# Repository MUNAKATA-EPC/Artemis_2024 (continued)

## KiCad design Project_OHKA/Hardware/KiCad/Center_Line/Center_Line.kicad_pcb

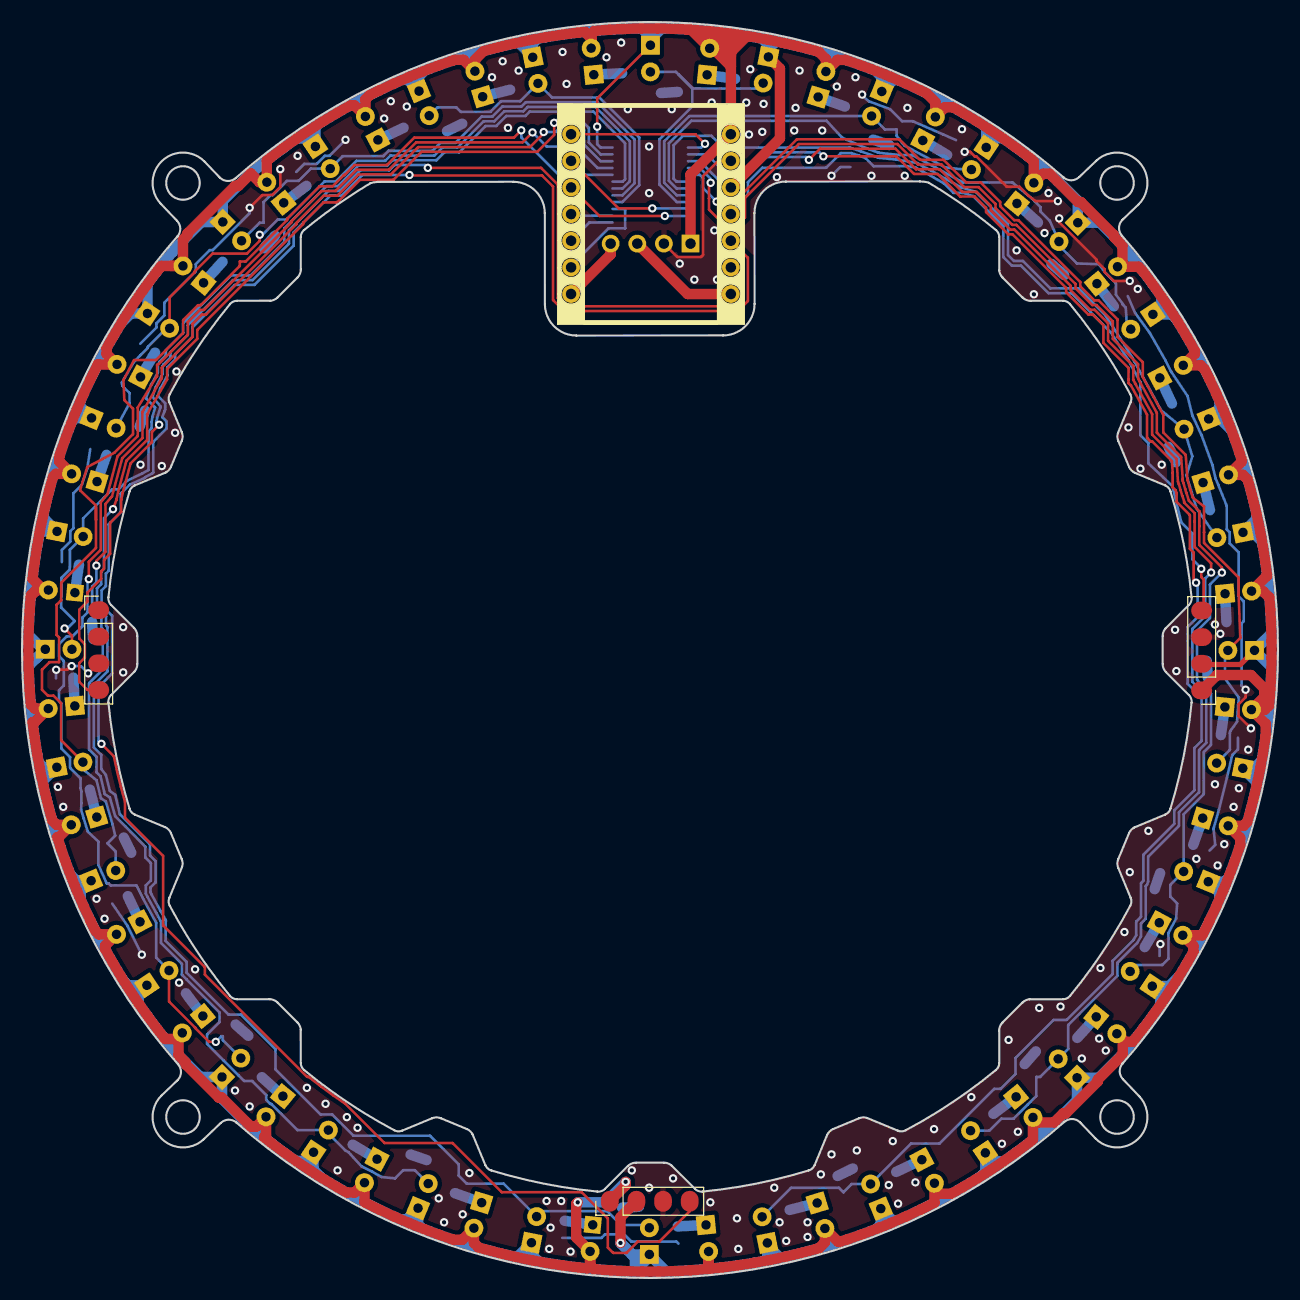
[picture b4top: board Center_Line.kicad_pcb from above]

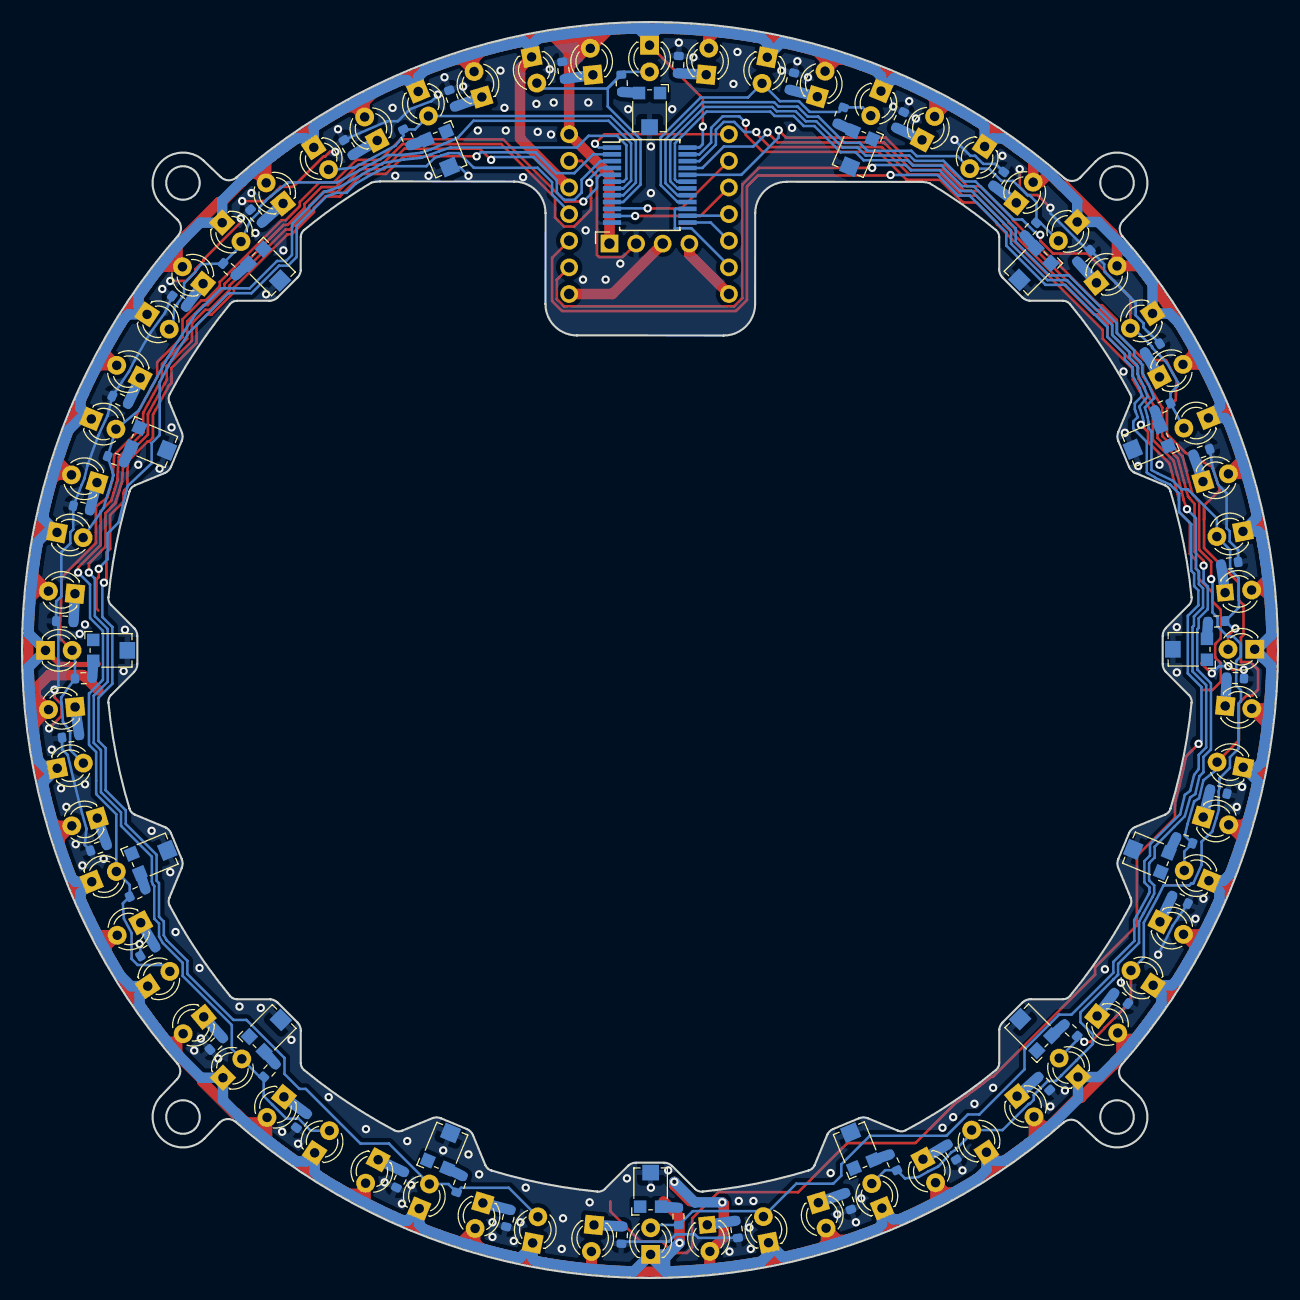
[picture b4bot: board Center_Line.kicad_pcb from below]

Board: 2 copper layers, 119.8 x 119.8 mm, 134 parts (130 on the bottom side), 78 nets.

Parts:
D1, D2, D3, D4, D5, D6, D7, D8, D9, D10, D11, D12, D13, D14, D15, D16, D17, D18, D19, D20, D21, D22, D23, D24, D25, D26, D27, D28, D29, D30, D31, D32: LED; LED_D3.0mm_Clear
J1: Conn_01x04_Socket; PinSocket_1x04_P2.54mm_Horizontal
J2, J3, J4: Conn_01x04_Socket; PinHeader_1x04_P2.54mm_Vertical
Q1, Q2, Q3, Q4, Q5, Q6, Q7, Q8, Q9, Q10, Q11, Q12, Q13, Q14, Q15, Q16, Q17, Q18, Q19, Q20, Q21, Q22, Q23, Q24, Q25, Q26, Q27, Q28, Q29, Q30, Q31, Q32: Q_Photo_NPN; LED_D3.0mm_Clear
R1, R2, R3, R4, R5, R6, R7, R8, R9, R10, R11, R12, R13, R14, R15, R16, R17, R18, R19, R20, R21, R22, R23, R24, R25, R26, R27, R28, R29, R30, R31, R32, R33, R34, R35, R36, R37, R38, R39, R40, R41, R42, R43, R44, R45, R46, R47, R48: R; R_0603_1608Metric
RV1, RV2, RV3, RV4, RV5, RV6, RV7, RV8, RV9, RV10, RV11, RV12, RV13, RV14, RV15, RV16: R_Potentiometer_Trim_US; Potentiometer_Bourns_TC33X_Vertical
U1: CD74HC4067SM; SSOP-24_5.3x8.2mm_P0.65mm
U2: Seeeduino_Xiao; seeeduinoXIAO

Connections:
+3.3V: J2.2, J3.2, J4.2, Q1.1 (C), Q2.1 (C), Q3.1 (C), Q4.1 (C), Q5.1 (C), Q6.1 (C), Q7.1 (C), Q8.1 (C), Q9.1 (C), Q10.1 (C), Q11.1 (C), Q12.1 (C), Q13.1 (C), Q14.1 (C), Q15.1 (C), Q16.1 (C), Q17.1 (C), Q18.1 (C), Q19.1 (C), Q20.1 (C), Q21.1 (C), Q22.1 (C), Q23.1 (C), Q24.1 (C), Q25.1 (C), Q26.1 (C), Q27.1 (C), Q28.1 (C), Q29.1 (C), Q30.1 (C), Q31.1 (C), Q32.1 (C), U1.24 (VCC), U2.12 (3V3)
+5V: D1.2 (A), D2.2 (A), D3.2 (A), D4.2 (A), D5.2 (A), D6.2 (A), D7.2 (A), D8.2 (A), D9.2 (A), D10.2 (A), D11.2 (A), D12.2 (A), D13.2 (A), D14.2 (A), D15.2 (A), D16.2 (A), D17.2 (A), D18.2 (A), D19.2 (A), D20.2 (A), D21.2 (A), D22.2 (A), D23.2 (A), D24.2 (A), D25.2 (A), D26.2 (A), D27.2 (A), D28.2 (A), D29.2 (A), D30.2 (A), D31.2 (A), D32.2 (A), J1.1, J2.1, J3.1, J4.1, U2.14 (5V)
/1: Q1.2 (E), Q2.2 (E), R33.2, U1.9 (I0)
/2: Q3.2 (E), Q4.2 (E), R34.2, U1.8 (I1)
/3: Q5.2 (E), Q6.2 (E), R35.2, U1.7 (I2)
/4: Q7.2 (E), Q8.2 (E), R36.2, U1.6 (I3)
/5: Q9.2 (E), Q10.2 (E), R37.2, U1.5 (I4)
/6: Q11.2 (E), Q12.2 (E), R38.2, U1.4 (I5)
/7: Q13.2 (E), Q14.2 (E), R39.2, U1.3 (I6)
/8: Q15.2 (E), Q16.2 (E), R40.2, U1.2 (I7)
/9: Q17.2 (E), Q18.2 (E), R41.2, U1.23 (I8)
/10: Q19.2 (E), Q20.2 (E), R42.2, U1.22 (I9)
/11: Q21.2 (E), Q22.2 (E), R43.2, U1.21 (I10)
/12: Q23.2 (E), Q24.2 (E), R44.2, U1.20 (I11)
/13: Q25.2 (E), Q26.2 (E), R45.2, U1.19 (I12)
/14: Q27.2 (E), Q28.2 (E), R46.2, U1.18 (I13)
/15: Q29.2 (E), Q30.2 (E), R47.2, U1.17 (I14)
/16: Q31.2 (E), Q32.2 (E), R48.2, U1.16 (I15)
/BACK: J4.4, U2.10 (MISO)
/E: U1.15 (~E), U2.6 (SCL)
/LEFT: J3.4, U2.11 (MOSI)
/LINE_RX: J1.4, U2.7 (TX)
/LINE_TX: J1.3, U2.8 (RX)
/RIGHT: J2.4, U2.9 (SCK)
/S0: U1.10 (S0), U2.2
/S1: U1.11 (S1), U2.3
/S2: U1.14 (S2), U2.4
/S3: U1.13 (S3), U2.5 (SDA)
/com: U1.1 (COM), U2.1 (DAC)
GND: J1.2, J2.3, J3.3, J4.3, R1.1, R2.1, R3.1, R4.1, R5.1, R6.1, R7.1, R8.1, R9.1, R10.1, R11.1, R12.1, R13.1, R14.1, R15.1, R16.1, R17.1, R18.1, R19.1, R20.1, R21.1, R22.1, R23.1, R24.1, R25.1, R26.1, R27.1, R28.1, R29.1, R30.1, R31.1, R32.1, RV1.2, RV2.2, RV3.2, RV4.2, RV5.2, RV6.2, RV7.2, RV8.2, RV9.2, RV10.2, RV11.2, RV12.2, RV13.2, RV14.2, RV15.2, RV16.2, U1.12 (GND), U2.13 (GND)
unnamed: D1.1 (K), R1.2
unnamed: D2.1 (K), R2.2
unnamed: D3.1 (K), R3.2
unnamed: D4.1 (K), R4.2
unnamed: D5.1 (K), R5.2
unnamed: D6.1 (K), R6.2
unnamed: D7.1 (K), R7.2
unnamed: D8.1 (K), R8.2
unnamed: D9.1 (K), R9.2
unnamed: D10.1 (K), R10.2
unnamed: D11.1 (K), R11.2
unnamed: D12.1 (K), R12.2
unnamed: D13.1 (K), R13.2
unnamed: D14.1 (K), R14.2
unnamed: D15.1 (K), R15.2
unnamed: D16.1 (K), R16.2
unnamed: D17.1 (K), R17.2
unnamed: D18.1 (K), R18.2
unnamed: D19.1 (K), R19.2
unnamed: D20.1 (K), R20.2
unnamed: D21.1 (K), R21.2
unnamed: D22.1 (K), R22.2
unnamed: D23.1 (K), R23.2
unnamed: D24.1 (K), R24.2
unnamed: D25.1 (K), R25.2
unnamed: D26.1 (K), R26.2
unnamed: D27.1 (K), R27.2
unnamed: D28.1 (K), R28.2
unnamed: D29.1 (K), R29.2
unnamed: D30.1 (K), R30.2
unnamed: D31.1 (K), R31.2
unnamed: D32.1 (K), R32.2
unnamed: R33.1, RV1.3
unnamed: R34.1, RV2.3
unnamed: R35.1, RV3.3
unnamed: R36.1, RV4.3
unnamed: R37.1, RV5.3
unnamed: R38.1, RV6.3
unnamed: R39.1, RV7.3
unnamed: R40.1, RV8.3
unnamed: R41.1, RV9.3
unnamed: R42.1, RV10.3
unnamed: R43.1, RV11.3
unnamed: R44.1, RV12.3
unnamed: R45.1, RV13.3
unnamed: R46.1, RV14.3
unnamed: R47.1, RV15.3
unnamed: R48.1, RV16.3

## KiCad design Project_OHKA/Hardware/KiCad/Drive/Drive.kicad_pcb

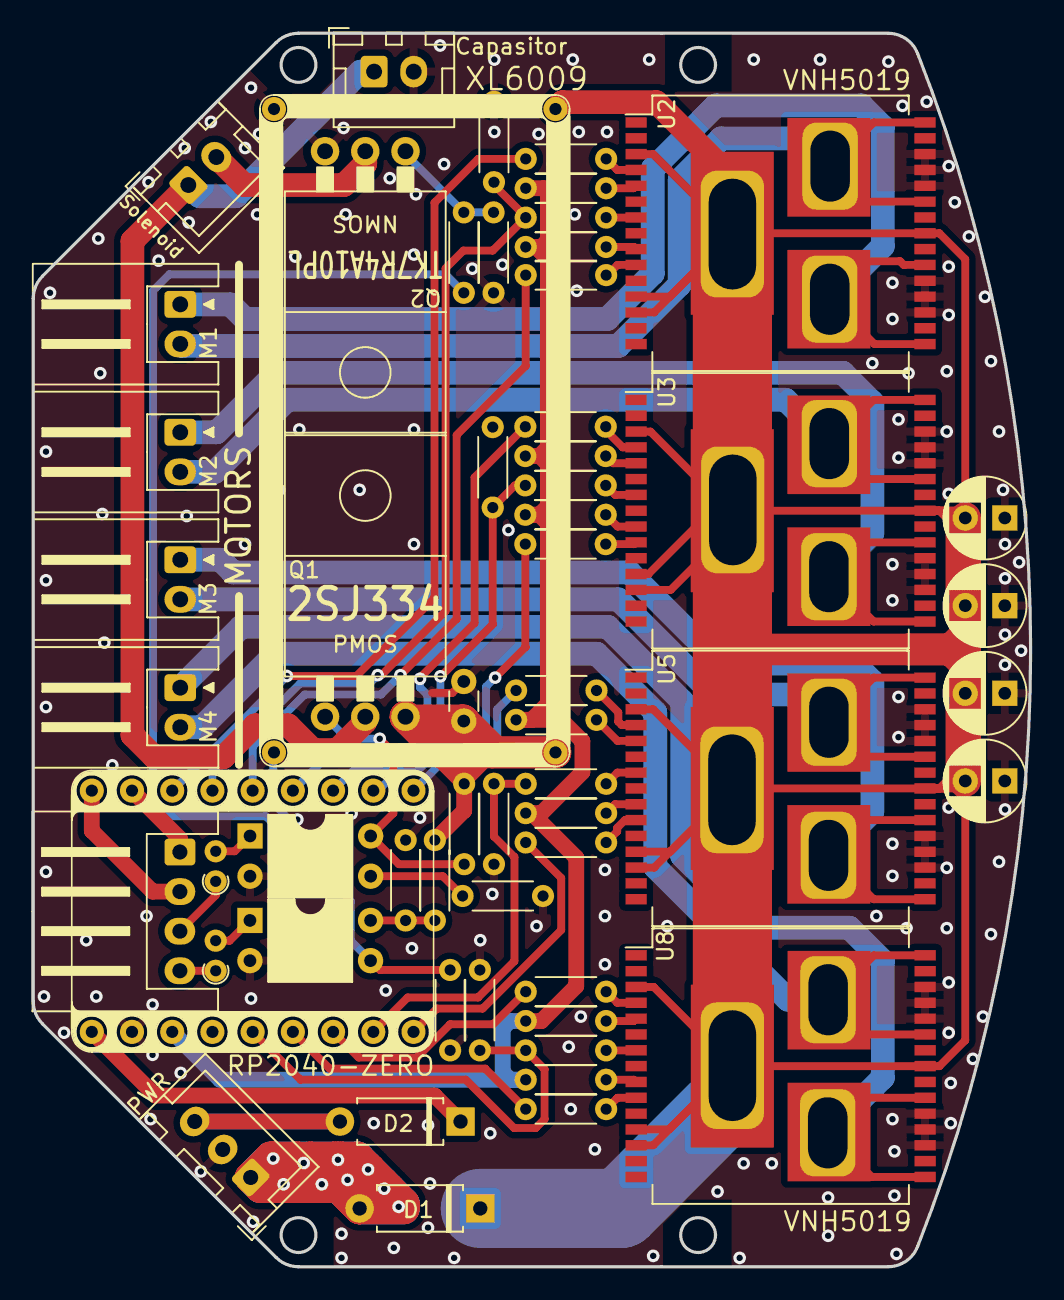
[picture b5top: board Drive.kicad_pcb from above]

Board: 2 copper layers, 63.0 x 77.9 mm, 58 parts (0 on the bottom side), 60 nets.

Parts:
C1, C2, C4, C5: C; CP_Radial_D5.0mm_P2.50mm
C3: C_Small; C_Disc_D3.0mm_W1.6mm_P2.50mm
Capasitor: C; JST_XH_B2B-XH-A_1x02_P2.50mm_Vertical
D1, D2: D; D_A-405_P7.62mm_Horizontal
J2: Conn_01x04_Socket; JST_XH_S4B-XH-A_1x04_P2.50mm_Horizontal
M1, M2, M3, M4: Conn_01x02_Socket; JST_XH_S2B-XH-A_1x02_P2.50mm_Horizontal
PWR: Conn_01x03_Socket; JST_XH_B3B-XH-A_1x03_P2.50mm_Vertical
Q1: PMOS; K15A20D
Q2: NMOS; K15A20D
R1, R7, R13, R21, R33: 10k; R_Axial_DIN0204_L3.6mm_D1.6mm_P5.08mm_Horizontal
R2, R6, R8, R12, R14, R18, R22, R28: 4.7k; R_Axial_DIN0204_L3.6mm_D1.6mm_P5.08mm_Horizontal
R3, R4, R5, R9, R10, R11, R15, R16, R17, R23, R24, R25, R26, R27, R31: 1k; R_Axial_DIN0204_L3.6mm_D1.6mm_P5.08mm_Horizontal
R19, R20: 330; R_Axial_DIN0204_L3.6mm_D1.6mm_P1.90mm_Vertical
R29, R30: 2k; R_Axial_DIN0204_L3.6mm_D1.6mm_P5.08mm_Horizontal
R32: 330; R_Axial_DIN0204_L3.6mm_D1.6mm_P5.08mm_Horizontal
Solenoid: Conn_01x02_Socket; JST_XH_B2B-XH-A_1x02_P2.50mm_Vertical
U1: RP2040_ZERO
U2, U3, U5, U8: VNH5019A-E; ST_MultiPowerSO-30
U4: XL6009
U6, U7: FODM217A; DIP-4_W7.62mm

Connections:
+3.3V: R2.2, R6.2, R8.2, R12.2, R14.2, R18.2, R22.2, R28.2, U1.3 (3.3v)
+5V: D2.1 (K), U1.1 (5v)
+12V: C1.2, C2.2, C4.2, C5.2, D1.1 (K), U2.3 (VCC), U2.12 (VBAT), U2.13 (VCC), U2.23 (VCC), U2.31 (VCC), U3.3 (VCC), U3.12 (VBAT), U3.13 (VCC), U3.23 (VCC), U3.31 (VCC), U4.1 (IN+), U5.3 (VCC), U5.12 (VBAT), U5.13 (VCC), U5.23 (VCC), U5.31 (VCC), U8.3 (VCC), U8.12 (VBAT), U8.13 (VCC), U8.23 (VCC), U8.31 (VCC)
+48V: C3.1, Q1.3 (S), R26.2, R30.1, U4.3 (OUT+)
/FET1: J2.3, R19.1
/FET2: J2.4, R20.1
/INA_1: R3.2, U1.21 (GP2/SDA)
/INA_2: R9.2, U1.18 (GP5/RX1/SCl)
/INA_3: R15.2, U1.15 (GP8/TX1/SDA)
/INA_4: R23.2, U1.7 (GP26/ADC0/SDA)
/INB_1: R4.2, U1.19 (GP4/TX1/SDA)
/INB_2: R10.2, U1.16 (GP7/SCL)
/INB_3: R16.2, U1.9 (GP14/SDA)
/INB_4: R24.2, U1.6 (GP27/ADC1/SCL)
/MD_RX: J2.2, U1.23 (GP0/TX0/SDA)
/MD_TX: J2.1, U1.22 (GP1/RX0/SCL)
/OUTA_1: M1.2, U2.1 (OUTA), U2.25 (OUTA), U2.30 (OUTA), U2.33 (OUTA)
/OUTA_2: M2.2, U3.1 (OUTA), U3.25 (OUTA), U3.30 (OUTA), U3.33 (OUTA)
/OUTA_3: M3.2, U5.1 (OUTA), U5.25 (OUTA), U5.30 (OUTA), U5.33 (OUTA)
/OUTA_4: M4.2, U8.1 (OUTA), U8.25 (OUTA), U8.30 (OUTA), U8.33 (OUTA)
/OUTB_1: M1.1, U2.15 (OUTB), U2.16 (OUTB), U2.21 (OUTB), U2.32 (OUTB)
/OUTB_2: M2.1, U3.15 (OUTB), U3.16 (OUTB), U3.21 (OUTB), U3.32 (OUTB)
/OUTB_3: M3.1, U5.15 (OUTB), U5.16 (OUTB), U5.21 (OUTB), U5.32 (OUTB)
/OUTB_4: M4.1, U8.15 (OUTB), U8.16 (OUTB), U8.21 (OUTB), U8.32 (OUTB)
/PWM_1: R1.1, R5.2, U1.20 (GP3/SCL)
/PWM_2: R7.1, R11.2, U1.17 (GP6/SDA)
/PWM_3: R13.1, R17.2, U1.8 (GP15/SCL)
/PWM_4: R21.1, R25.2, U1.5 (GP28/ADC2)
/Solenoid+: Capasitor.1, Q1.1 (D), Solenoid.1
/Solenoid-: Q2.1 (D), Solenoid.2
GND: C1.1, C2.1, C3.2, C4.1, C5.1, Capasitor.2, PWR.2, Q2.3 (S), R1.2, R7.2, R13.2, R21.2, R27.1, R29.2, R31.1, R33.1, U1.2 (GND), U2.18 (GNDB), U2.19 (GNDB), U2.20 (GNDB), U2.26 (GNDA), U2.27 (GNDA), U2.28 (GNDA), U3.18 (GNDB), U3.19 (GNDB), U3.20 (GNDB), U3.26 (GNDA), U3.27 (GNDA), U3.28 (GNDA), U4.2 (IN-), U4.4 (OUT-), U5.18 (GNDB), U5.19 (GNDB), U5.20 (GNDB), U5.26 (GNDA), U5.27 (GNDA), U5.28 (GNDA), U6.2, U7.2, U8.18 (GNDB), U8.19 (GNDB), U8.20 (GNDB), U8.26 (GNDA), U8.27 (GNDA), U8.28 (GNDA)
unnamed: D1.2 (A), PWR.1
unnamed: D2.2 (A), PWR.3
unnamed: Q1.2 (G), R26.1, U6.4
unnamed: Q2.2 (G), R32.2, R33.2
unnamed: R19.2, U6.1
unnamed: R20.2, U7.1
unnamed: R27.2, R32.1, U7.3
unnamed: R29.1, U6.3
unnamed: R30.2, R31.2, U7.4
unnamed: R2.1, U2.5 (EN/DIAGA)
unnamed: R6.1, U2.9 (EN/DIAGB)
unnamed: R3.1, U2.4 (INA)
unnamed: R4.1, U2.10 (INB)
unnamed: R5.1, U2.7 (PWM)
unnamed: R8.1, U3.5 (EN/DIAGA)
unnamed: R12.1, U3.9 (EN/DIAGB)
unnamed: R9.1, U3.4 (INA)
unnamed: R10.1, U3.10 (INB)
unnamed: R11.1, U3.7 (PWM)
unnamed: R14.1, U5.5 (EN/DIAGA)
unnamed: R18.1, U5.9 (EN/DIAGB)
unnamed: R15.1, U5.4 (INA)
unnamed: R16.1, U5.10 (INB)
unnamed: R17.1, U5.7 (PWM)
unnamed: R22.1, U8.5 (EN/DIAGA)
unnamed: R28.1, U8.9 (EN/DIAGB)
unnamed: R23.1, U8.4 (INA)
unnamed: R24.1, U8.10 (INB)
unnamed: R25.1, U8.7 (PWM)

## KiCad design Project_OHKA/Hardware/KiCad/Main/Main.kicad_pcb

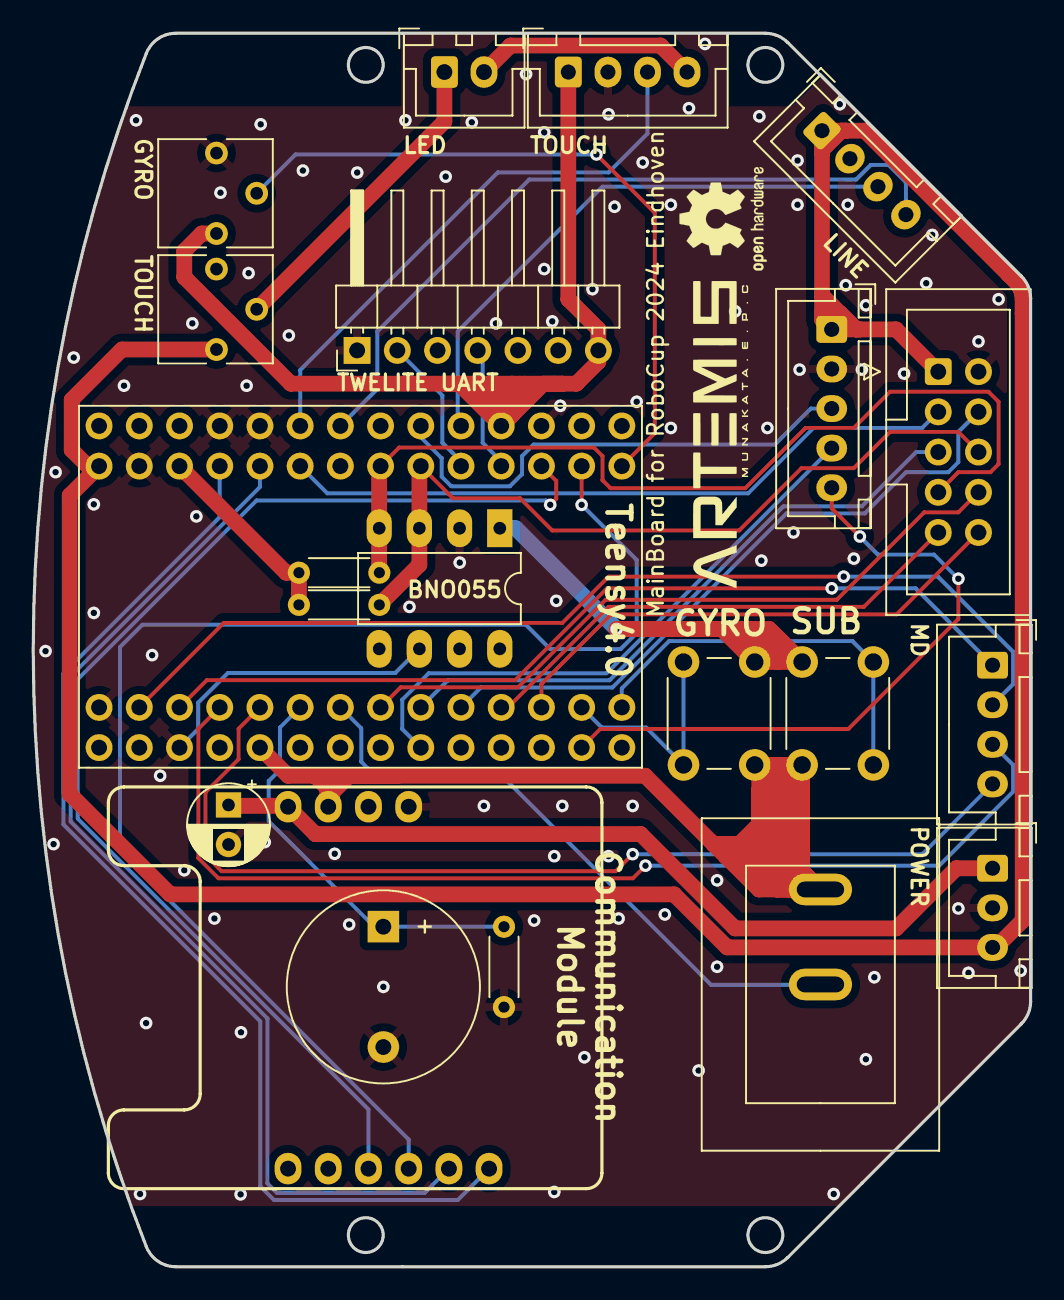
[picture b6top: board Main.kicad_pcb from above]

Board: 2 copper layers, 63.0 x 77.9 mm, 21 parts (0 on the bottom side), 35 nets.

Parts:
BZ1: Buzzer; Buzzer_12x9.5RM7.6
C1: C; CP_Radial_D5.0mm_P2.50mm
J1: Conn_01x07_Socket; PinHeader_1x07_P2.54mm_Horizontal
J2: Conn_01x10_Socket; IDC-Header_2x05_P2.54mm_Vertical
J3, J5, J7: Conn_01x04_Socket; JST_XH_B4B-XH-A_1x04_P2.50mm_Vertical
J4: Conn_01x02_Socket; JST_XH_B2B-XH-A_1x02_P2.50mm_Vertical
J6: Conn_01x06_Socket; JST_XH_B5B-XH-A_1x05_P2.50mm_Vertical
J8: Conn_01x03_Socket; JST_XH_B3B-XH-A_1x03_P2.50mm_Vertical
R1, R2, R4: R; R_Axial_DIN0204_L3.6mm_D1.6mm_P5.08mm_Horizontal
R3: R_Trim; Potentiometer_Vishay_T73YP_Vertical
RV1: R_Potentiometer_Trim_US; Potentiometer_Vishay_T73YP_Vertical
SW1, SW2: SW_Push; SW_PUSH_6mm_H5mm
SW3: SW_Push; DS-850k
U1: BNO055; DIP-8_W7.62mm_LongPads
U2: comm_module
U3: Teensy4.0; Teensy_Brakeout

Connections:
+3.3V: J1.7, J3.1, R1.2, R2.2, RV1.1, SW1.2, SW2.2, SW3.2, U1.1 (VIN), U2.8 (LOGV), U3.31 (3V3)
+5V: J2.1, J5.1, J6.1, J8.3, R3.1, U3.33 (VIN)
+12V: C1.1, J8.1, U2.7 (VIN)
/01: U2.2 (01), U3.29 (22_A8_CTX1)
/02: U2.1 (02), U3.30 (23_A9_CRX1_MCLK1)
/CAM_RX: J2.3, U3.28 (21_A7_RX5_BCLK1)
/Comm_RX: U2.4 (TX), U3.22 (15_A1_RX3_SPDIF_IN)
/Comm_TX: U2.3 (RX), U3.21 (14_A0_TX3_SPDIF_OUT)
/FET1: J7.3, U3.4 (2_OUT2)
/FET2: J7.4, U3.5 (3_LRCLK2)
/GY_RES: SW1.1, U3.13 (11_MOSI_CTX1)
/GY_TRIM: RV1.2, U3.20 (13_SCK_CRX1_LED)
/IR_RX: J2.5, U3.9 (7_RX2_OUT1A)
/IR_TX: J2.4, U3.10 (8_TX2_IN1)
/K: J3.4, J4.2
/LEFT: J2.9, U3.11 (9_OUT1C)
/LINE_RX: J5.4, U3.36 (25_A11_RX6_SDA2)
/LINE_TX: J5.3, U3.35 (24_A10_TX6_SCL2)
/MD_RX: J7.2, U3.2 (0_RX1_CRX2_CS1)
/MD_TX: J7.1, U3.3 (1_TX1_CTX2_MISO1)
/RIGHT: J2.10, U3.12 (10_CS_MQSR)
/RUN: J2.8, U3.8 (6_OUT1D)
/SCL: J2.7, R2.1, U1.4 (SCL), U3.26 (19_A5_SCL0)
/SDA: J2.6, R1.1, U1.3 (SDA), U3.25 (18_A4_SDA0)
/SUB: SW2.1, U3.14 (12_MISO_MQSL)
/SUB_1: J6.5, U3.41 (30_CRX3)
/SUB_RX: J6.3, U3.39 (28_RX7)
/SUB_TX: J6.4, U3.40 (29_TX7)
/Start: SW3.1, U3.7 (5_IN2)
/TOUCH: J3.3, U3.38 (27_A13_SCK1)
/TWE_RX: J1.4, U3.23 (16_A2_RX4_SCL1)
/TWE_TX: J1.2, U3.24 (17_A3_TX4_SDA1)
GND: BZ1.2 (+), C1.2, J1.1, J2.2, J3.2, J5.2, J6.2, J8.2, R4.2, RV1.3, U1.2 (GND), U1.6 (GND), U2.10 (GND), U3.1 (GND)
unnamed: BZ1.1 (-), R4.1, U3.6 (4_BCLK2)
unnamed: J4.1, R3.2
